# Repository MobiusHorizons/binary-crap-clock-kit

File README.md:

This is a fairly crap clock kit made with CMOS logic, it is a fairly simple design and has the unique feature of being both difficult to read and difficult to set the time! Consider it a curiosity rather than a real timepiece, I cannot make any absolute guarantees about its accuracy but it is fairly good.

I made it as a challenge to myself more than anything else, an exercise in learning about CMOS logic and making my first kit.

It runs down to about 2.7-3v (0.5mA with LEDs and ~6µA without the LEDs running) and up to 6v and consumes very little current running at lower voltages. In fact, you could run it for years on 2AA batteries with the LEDs disabled. At 3v the LEDs are fairly dim but at 5v they will dazzle you, choose your poison.

I haven't included extensive instructions, it should be fairly self-explanatory... that said, I mess stuff up all the time. So with that in mind, here is a video of me building it. I realise this could be a bit of a slog to watch so feel free to just wing it.

<iframe class="embed-responsive-item" src="https://www.youtube.com/embed/5j2Psmb9NmE?feature=oembed&amp;wmode=transparent"></iframe>

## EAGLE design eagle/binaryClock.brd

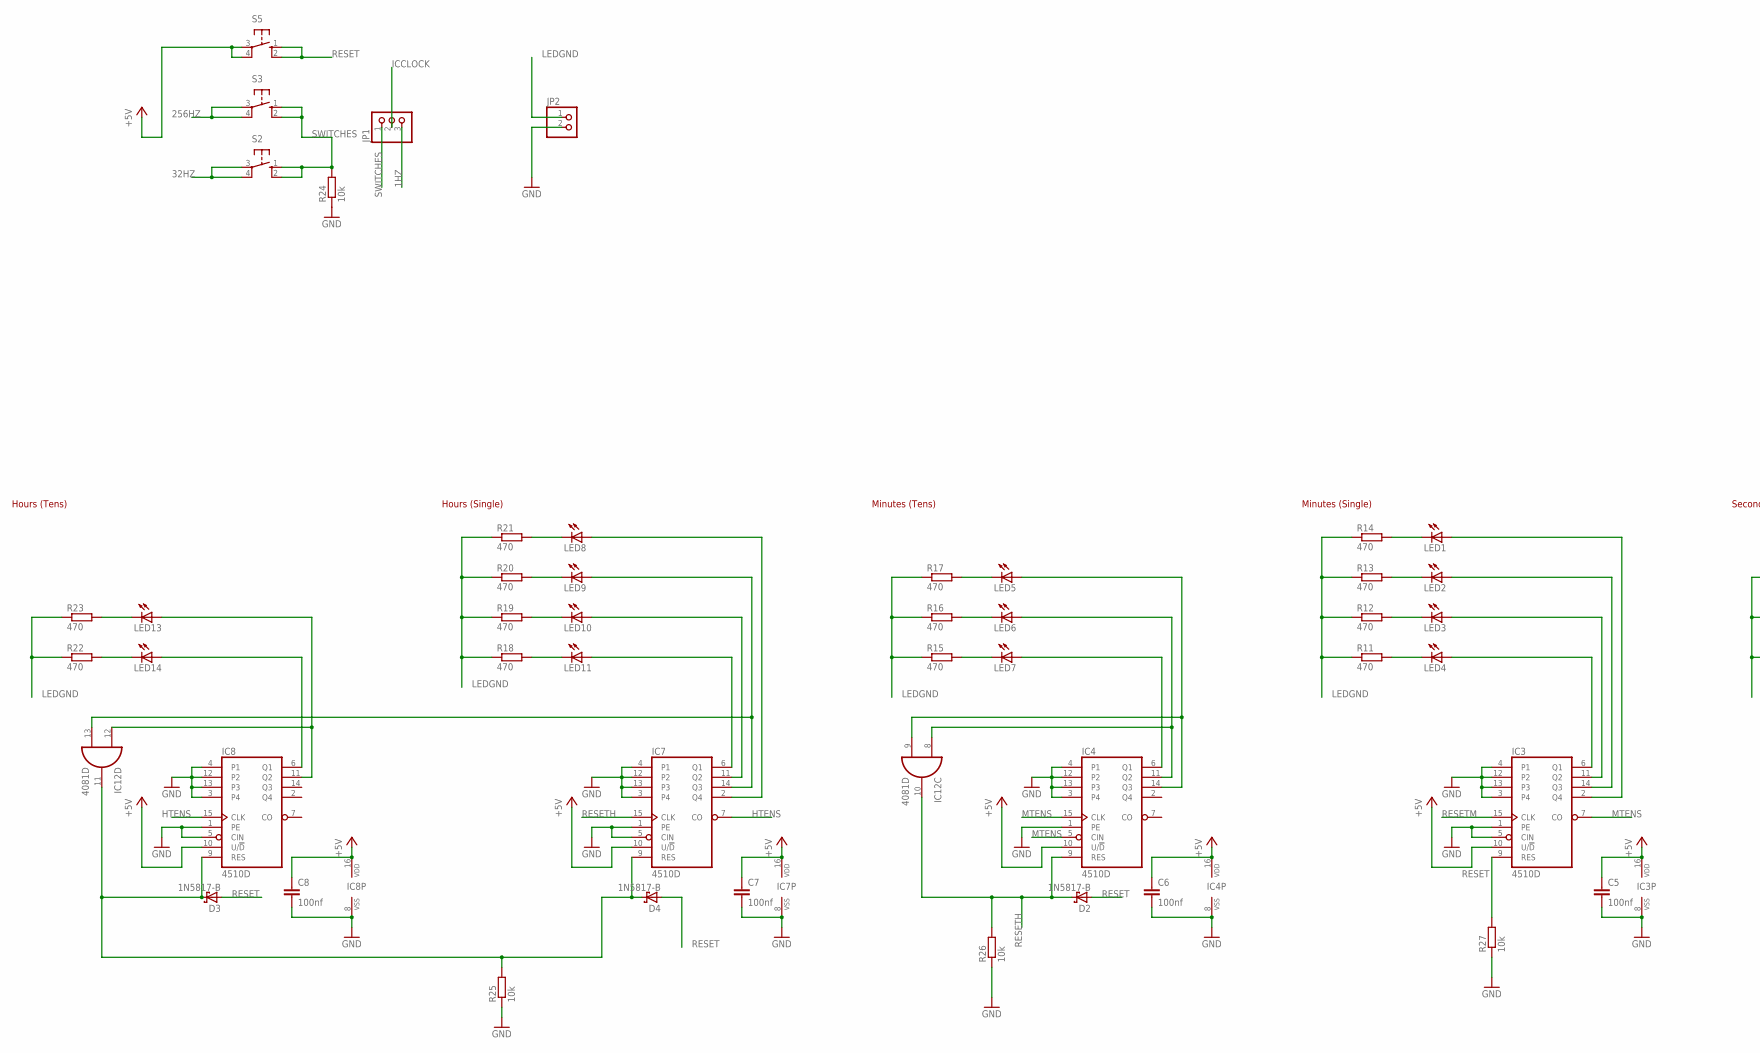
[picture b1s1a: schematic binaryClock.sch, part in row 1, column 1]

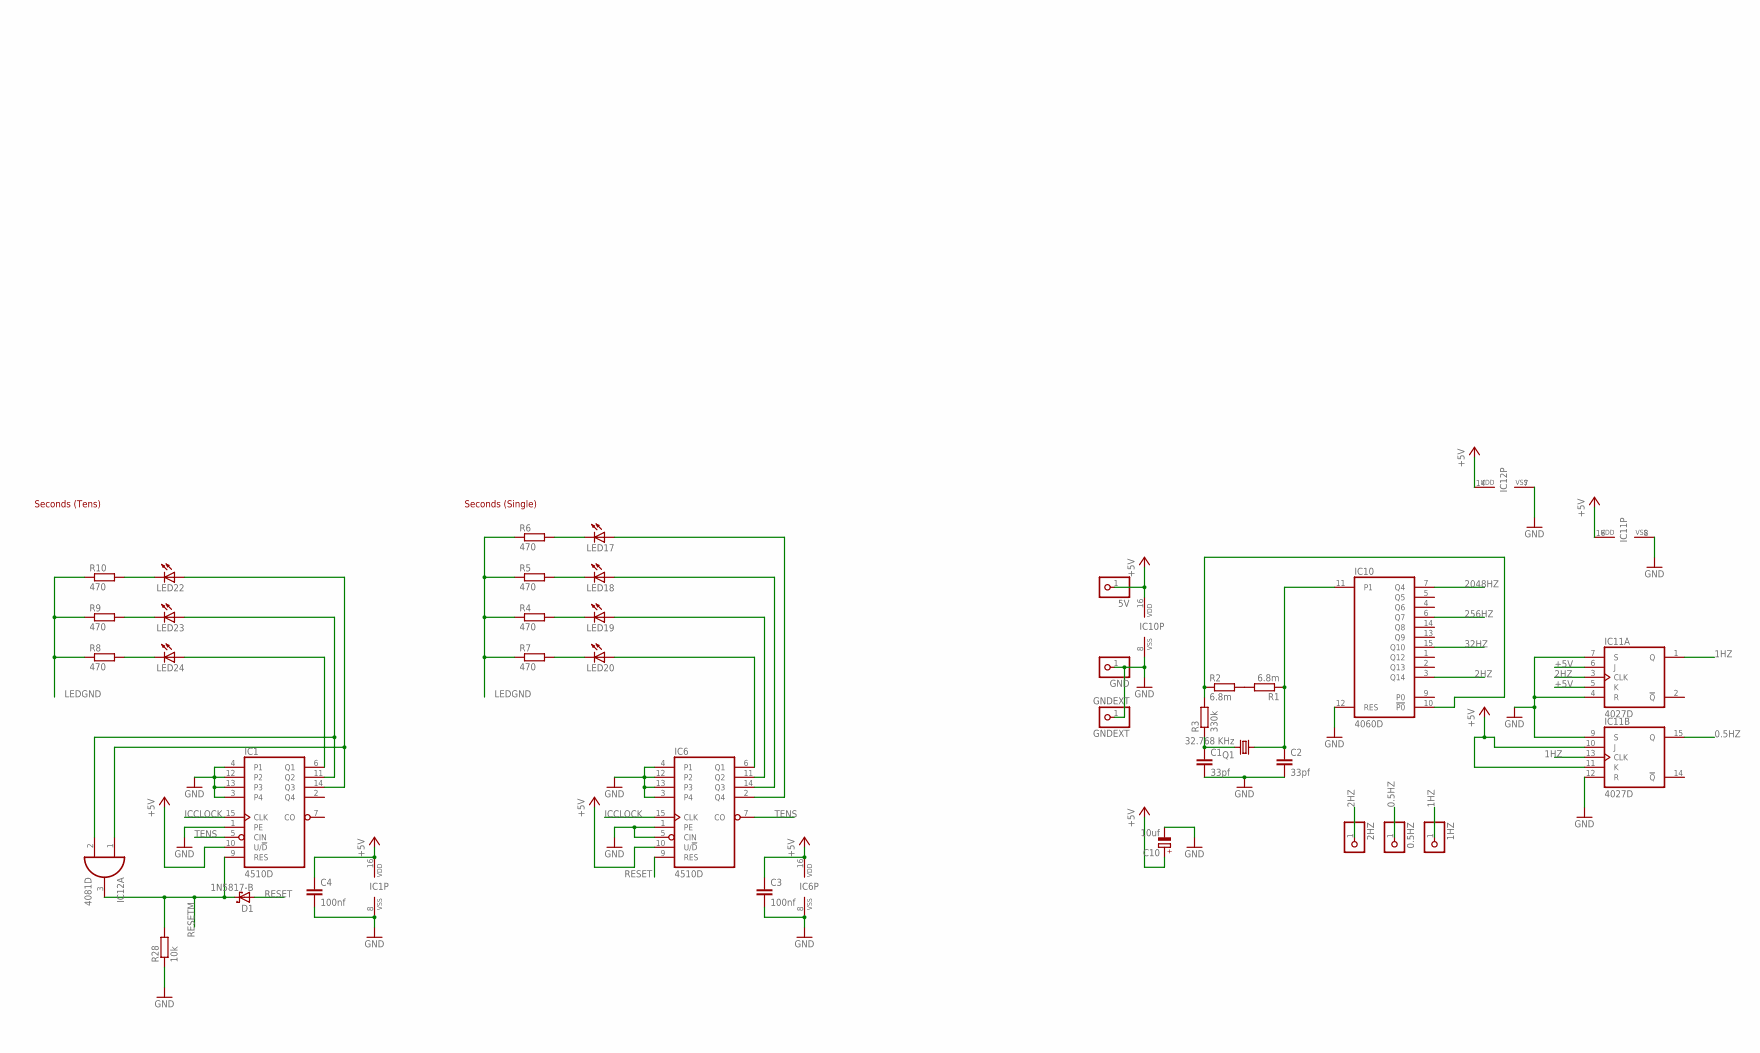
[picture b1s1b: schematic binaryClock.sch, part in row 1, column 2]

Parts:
0.5HZ, 1HZ, 2HZ, 5V: PINHD-1X1; 1X01
C1, C2: 33pf; C025-030X050
C3, C4, C5, C6, C7, C8: 100nf; C025-030X050
C10: 10uf; E2,5-5
D1, D2, D3, D4: 1N5817-B; DO41-7.6
GND: PINHD-1X1; 1X01
GNDEXT: GNDEXT; 1X01
IC1, IC3, IC4, IC6, IC7, IC8: 4510D; SO16
IC10: 4060D; SO16
IC11: 4027D; SO16
IC12: 4081D; SO14
JP1: PINHD-1X3; 1X03
JP2: PINHD-1X2; 1X02
LED1, LED2, LED3, LED4, LED5, LED6, LED7, LED8, LED9, LED10, LED11, LED13, LED14, LED17, LED18, LED19, LED20, LED22, LED23, LED24: LED5MM
Q1: 32.768 KHz; TC26H
R1, R2: 6.8m; R0805
R3: 330k; R0805
R4, R5, R6, R7, R8, R9, R10, R11, R12, R13, R14, R15, R16, R17, R18, R19, R20, R21, R22, R23: 470; R0805
R24, R25, R26, R27, R28: 10k; R0805
S2, S3, S5: 10-XX; B3F-10XX

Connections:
0.5HZ: 0.5HZ.1, IC11.15 (Q)
1HZ: 1HZ.1, IC11.1 (Q), IC11.13 (CLK), JP1.3
2HZ: 2HZ.1, IC10.3 (Q14), IC11.3 (CLK)
32HZ: IC10.15 (Q10), S2.3, S2.4 (P1)
256HZ: IC10.6 (Q7), S3.3, S3.4 (P1)
2048HZ: IC10.7 (Q4)
+5V: 5V.1, C3.1, C4.1, C5.1, C6.1, C7.1, C8.1, C10.+, IC1.10 (U/!D), IC1.16 (VDD), IC3.10 (U/!D), IC3.16 (VDD), IC4.10 (U/!D), IC4.16 (VDD), IC6.10 (U/!D), IC6.16 (VDD), IC7.10 (U/!D), IC7.16 (VDD), IC8.10 (U/!D), IC8.16 (VDD), IC10.16 (VDD), IC11.5 (K), IC11.6 (J), IC11.10 (J), IC11.11 (K), IC11.16 (VDD), IC12.14 (VDD), S5.3, S5.4 (P1)
GND: C1.2, C2.2, C3.2, C4.2, C5.2, C6.2, C7.2, C8.2, C10.-, GND.1, GNDEXT.1, IC1.1 (PE), IC1.3 (P4), IC1.4 (P1), IC1.8 (VSS), IC1.12 (P2), IC1.13 (P3), IC3.1 (PE), IC3.3 (P4), IC3.4 (P1), IC3.5 (CIN), IC3.8 (VSS), IC3.12 (P2), IC3.13 (P3), IC4.1 (PE), IC4.3 (P4), IC4.4 (P1), IC4.8 (VSS), IC4.12 (P2), IC4.13 (P3), IC6.1 (PE), IC6.3 (P4), IC6.4 (P1), IC6.5 (CIN), IC6.8 (VSS), IC6.12 (P2), IC6.13 (P3), IC7.1 (PE), IC7.3 (P4), IC7.4 (P1), IC7.5 (CIN), IC7.8 (VSS), IC7.12 (P2), IC7.13 (P3), IC8.1 (PE), IC8.3 (P4), IC8.4 (P1), IC8.5 (CIN), IC8.8 (VSS), IC8.12 (P2), IC8.13 (P3), IC10.8 (VSS), IC10.12 (RES), IC11.4 (R), IC11.7 (S), IC11.8 (VSS), IC11.9 (S), IC11.12 (R), IC12.7 (VSS), JP2.2, R24.1, R25.1, R26.1, R27.1, R28.1
HTENS: IC7.7 (CO), IC8.15 (CLK)
ICCLOCK: IC1.15 (CLK), IC6.15 (CLK), JP1.2
LEDGND: JP2.1, R4.1, R5.1, R6.1, R7.1, R8.1, R9.1, R10.1, R11.1, R12.1, R13.1, R14.1, R15.1, R16.1, R17.1, R18.1, R19.1, R20.1, R21.1, R22.1, R23.1
MTENS: IC3.7 (CO), IC4.5 (CIN), IC4.15 (CLK)
unnamed: IC6.6 (Q1), LED20.A
unnamed: IC6.11 (Q2), LED19.A
unnamed: R1.2, R2.2
unnamed: C1.1, Q1.2, R3.1
unnamed: IC10.10 (!P0), R2.1, R3.2
unnamed: C2.1, IC10.11 (P1), Q1.1, R1.1
unnamed: IC6.14 (Q3), LED18.A
unnamed: IC6.2 (Q4), LED17.A
unnamed: LED17.K (C), R6.2
unnamed: LED18.K (C), R5.2
unnamed: LED19.K (C), R4.2
unnamed: LED20.K (C), R7.2
unnamed: IC1.6 (Q1), LED24.A
unnamed: IC1.11 (Q2), IC12.2 (I1), LED23.A
unnamed: IC1.14 (Q3), IC12.1 (I0), LED22.A
unnamed: D3.C, D4.C, IC7.9 (RES), IC8.9 (RES), IC12.11 (O), R25.2
unnamed: IC7.6 (Q1), LED11.A
unnamed: LED22.K (C), R10.2
unnamed: LED23.K (C), R9.2
unnamed: LED24.K (C), R8.2
unnamed: IC7.11 (Q2), LED10.A
unnamed: IC3.6 (Q1), LED4.A
unnamed: IC3.11 (Q2), LED3.A
unnamed: IC3.14 (Q3), LED2.A
unnamed: IC3.2 (Q4), LED1.A
unnamed: LED1.K (C), R14.2
unnamed: LED2.K (C), R13.2
unnamed: LED3.K (C), R12.2
unnamed: LED4.K (C), R11.2
unnamed: IC4.6 (Q1), LED7.A
unnamed: IC4.11 (Q2), IC12.8 (I0), LED6.A
unnamed: IC4.14 (Q3), IC12.9 (I1), LED5.A
unnamed: LED5.K (C), R17.2
unnamed: LED6.K (C), R16.2
unnamed: LED7.K (C), R15.2
unnamed: IC7.14 (Q3), IC12.13 (I1), LED9.A
unnamed: IC7.2 (Q4), LED8.A
unnamed: LED8.K (C), R21.2
unnamed: LED9.K (C), R20.2
unnamed: LED10.K (C), R19.2
unnamed: LED11.K (C), R18.2
unnamed: IC8.6 (Q1), LED14.A
unnamed: IC8.11 (Q2), IC12.12 (I0), LED13.A
unnamed: LED13.K (C), R23.2
unnamed: LED14.K (C), R22.2
RESET: D1.A, D2.A, D3.A, D4.A, IC3.9 (RES), IC6.9 (RES), R27.2, S5.1 (S), S5.2 (S1)
RESETH: D2.C, IC4.9 (RES), IC7.15 (CLK), IC12.10 (O), R26.2
RESETM: D1.C, IC1.9 (RES), IC3.15 (CLK), IC12.3 (O), R28.2
SWITCHES: JP1.1, R24.2, S2.1 (S), S2.2 (S1), S3.1 (S), S3.2 (S1)
TENS: IC1.5 (CIN), IC6.7 (CO)

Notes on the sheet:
Seconds (Single)
Seconds (Tens)
Minutes (Single)
Minutes (Tens)
Hours (Single)
Hours (Tens)

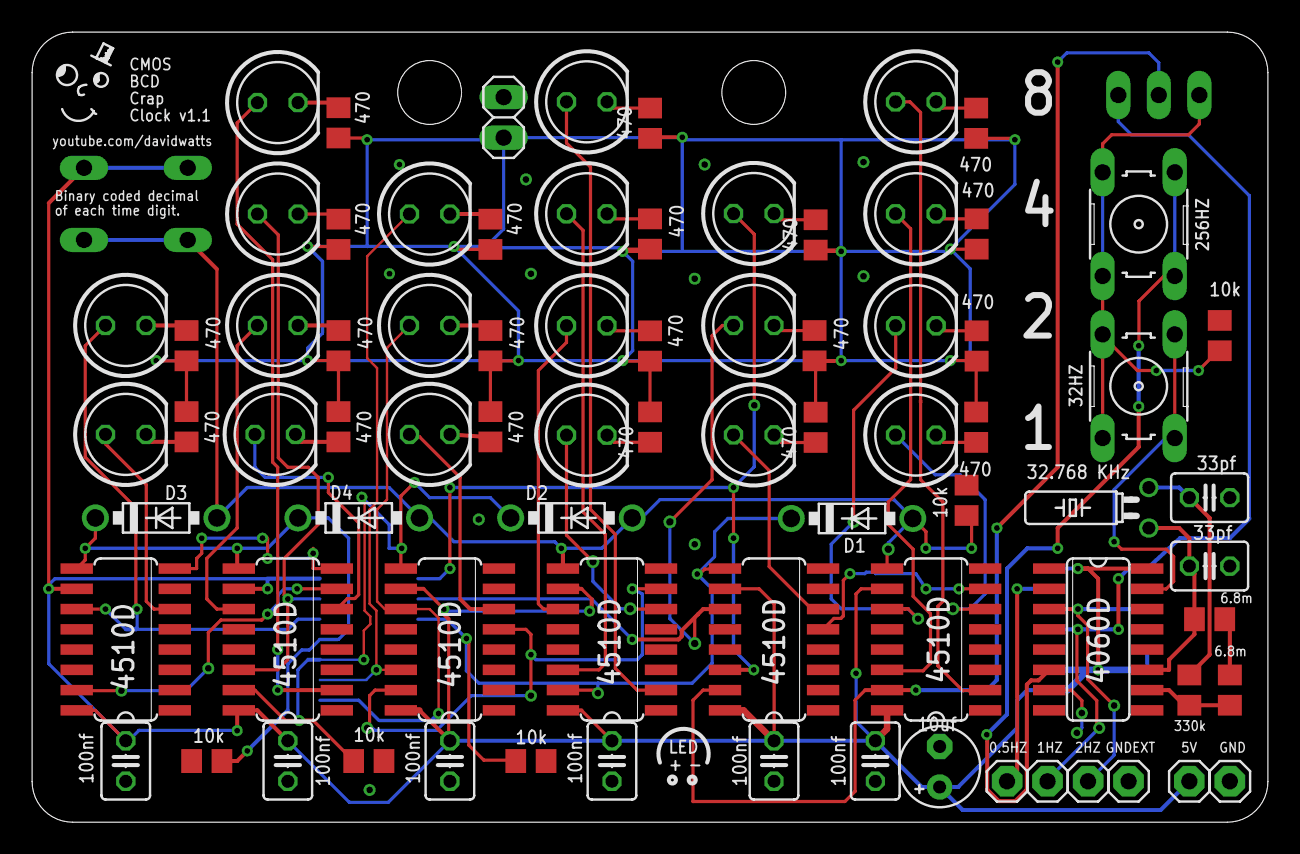
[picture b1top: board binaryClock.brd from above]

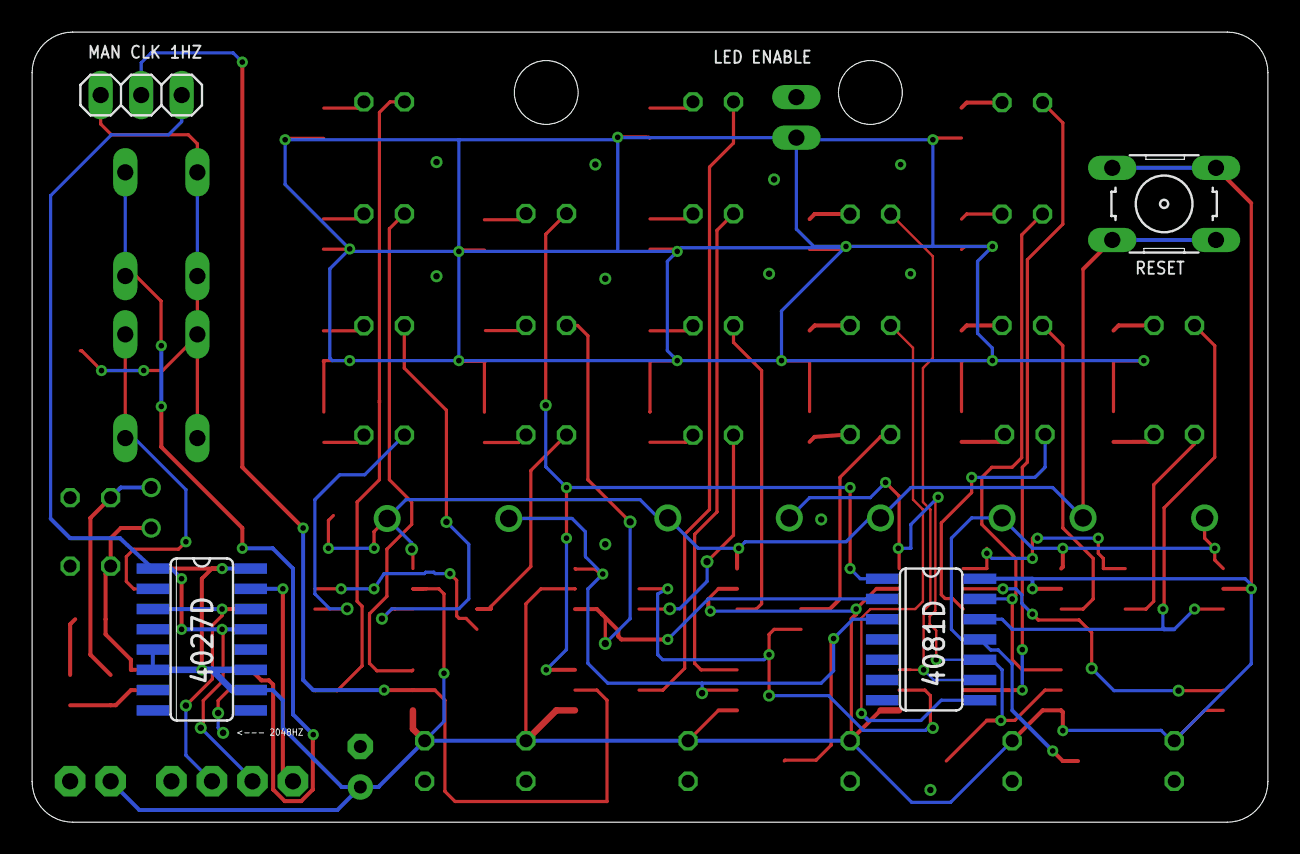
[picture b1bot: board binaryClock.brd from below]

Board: 2 copper layers, 77.5 x 49.5 mm, 82 parts (4 on the bottom side), 61 nets.

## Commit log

2018-04-26 Initial Commit with WIP BOM
2018-04-26 Updated color
2018-04-27 added Readme based on tindie page
2018-04-27 Updated bom
2018-04-27 updated bom and added drill file
2019-12-30 Re-plot gerbers using eagle 9
